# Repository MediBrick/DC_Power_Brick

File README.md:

# Power Brick

The Power Brick can control power to resistive heater, thermo electric cooler/heater or DC motor.
It requires 8V or larger input and might be able to handle 30A (4 oz copper).

## Two Channel DC Power Controller.
  - DRV8704 FET driver
  -  8..52V
  -  SPI interface for  monitoring
  -  PWM 500kHz
  -  CSD18540Q5B FET 30 / 400A (peak)

[Datasheet Driver](./datasheets/drv8704.pdf)
[Datasheet FET](./datasheets/csd18540q5b.pdf)

### Overview

### Control Logic

## 2x Two Channel Precision Thermistor ADC
  - ADS1220
  - Configured for two channel 10K NTC thermistor measurements using internal current source and external reference 22k resistor.

[Datasheet ADS1220](./datasheets/ads1220.pdf)

This design requires that both temperature sensors are attached. If one is not populated, the measurement circuit is interrupted and no temperature is reported.

## Power Brick PCB Design

The following files were created for this project using KiCad.

[Bill of Materials](./DC%20Power%20Brick%20BOM.xlsx)
[Gerber Files](./)

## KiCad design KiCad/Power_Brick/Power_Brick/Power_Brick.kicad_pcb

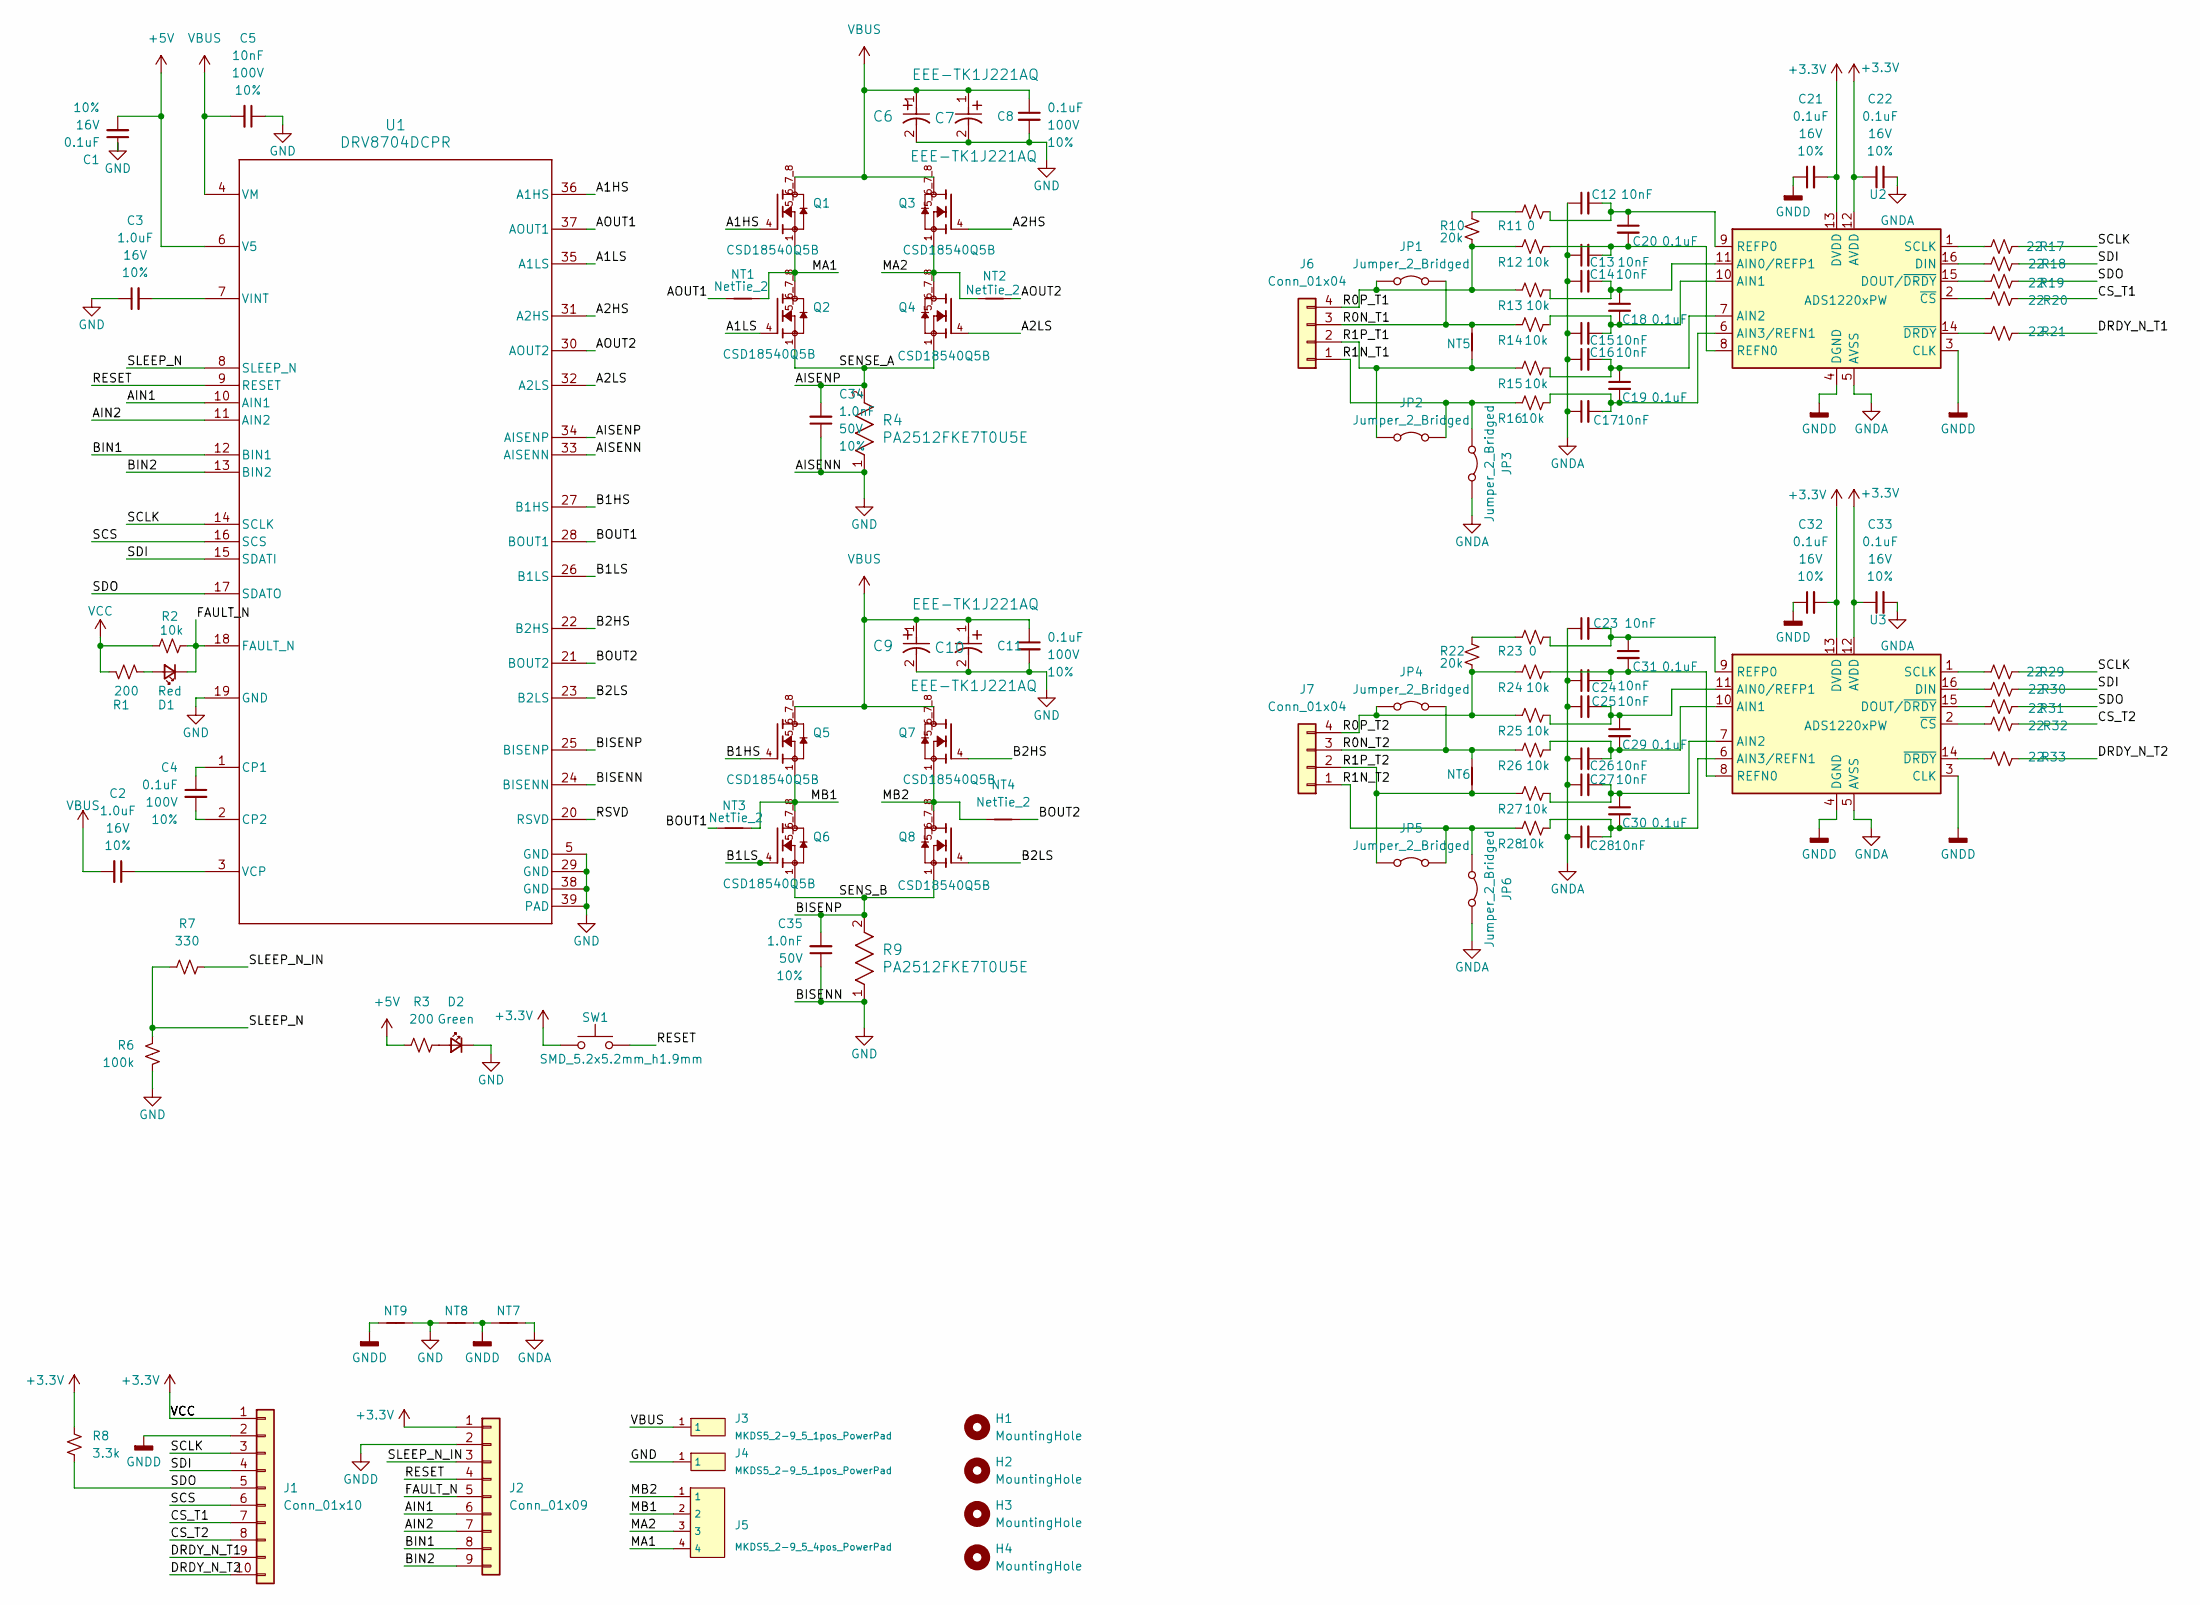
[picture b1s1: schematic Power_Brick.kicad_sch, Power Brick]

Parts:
C1, C18, C19, C20, C21, C22, C29, C30, C31, C32, C33: 0.1uF; C_0402_1005Metric; Voltage 16V; Tolerance 10%
C2, C3: 1.0uF; C_0402_1005Metric; Voltage 16V; Tolerance 10%
C4, C8, C11: 0.1uF; C_0603_1608Metric; Voltage 100V; Tolerance 10%
C5: 10nF; C_0402_1005Metric; Voltage 100V; Tolerance 10%
C6, C7, C9, C10: EEE-TK1J221AQ; CAP_PAN_EEE_H13_PAN
C12, C13, C14, C15, C16, C17, C23, C24, C25, C26, C27, C28: 10nF; C_0402_1005Metric; Voltage 50V; Tolerance 10%
C34, C35: 1.0nF; C_0402_1005Metric; Voltage 50V; Tolerance 10%
D1: Red; LED_0603_1608Metric_Red
D2: Green; LED_0603_1608Metric_Green
H1, H2, H3, H4: MountingHole; MountingHole_3.2mm_M3
J1: Conn_01x10; PinHeader_1x10_P2.54mm_Vertical
J2: Conn_01x09; PinHeader_1x09_P2.54mm_Vertical
J3, J4: MKDS5_2-9_5_1pos_PowerPad
J5: MKDS5_2-9_5_4pos_PowerPad
J6, J7: Conn_01x04; PinHeader_1x04_P2.54mm_Vertical
JP1, JP2, JP3, JP4, JP5, JP6: Jumper_2_Bridged; Jumper_2_NO
NT1, NT2, NT3, NT4, NT5, NT6: NetTie_2; NetTie-2_SMD_Pad0.25mm
NT7: NetTie_2; NetTie-2_SMD_Pad2.0mm
NT8, NT9: NetTie_2; NetTie-2_SMD_Pad0.5mm
Q1, Q2, Q3, Q4, Q5, Q6, Q7, Q8: CSD18540Q5B; TRANS_CSD18540Q5B; PARTREV B
R1, R3: 200; R_0402_1005Metric
R2, R12, R13, R14, R15, R16, R24, R25, R26, R27, R28: 10k; R_0402_1005Metric
R4, R9: PA2512FKE7T0U5E; RES_PA2512_YAG
R6: 100k; R_0402_1005Metric
R7: 330; R_0402_1005Metric
R8: 3.3k; R_0402_1005Metric
R10, R22: 20k; R_0402_1005Metric
R11, R23: 0; R_0402_1005Metric
R17, R18, R19, R20, R21, R29, R30, R31, R32, R33: 22; R_0402_1005Metric
SW1: SMD_5.2x5.2mm_h1.9mm; Push_SMD_4.6x2.8mm_h1.9mm
U1: DRV8704DCPR; DCP0038A_N
U2, U3: ADS1220xPW; TSSOP-16_4.4x5mm_P0.65mm

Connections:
+3.3V: C21.2, C22.1, C32.2, C33.1, J1.1, J2.1, R1.2, R2.1, R8.1, SW1.1, U2.12 (AVDD), U2.13 (DVDD), U3.12 (AVDD), U3.13 (DVDD)
+5V: C1.2, R3.1, U1.6 (V5)
/A1HS: Q1.4, U1.36 (A1HS)
/A1LS: Q2.4, U1.35 (A1LS)
/A2HS: Q3.4, U1.31 (A2HS)
/A2LS: Q4.4, U1.32 (A2LS)
/AIN1: J2.6, U1.10 (AIN1)
/AIN2: J2.7, U1.11 (AIN2)
/AISENP: C34.2, Q2.1, Q2.2, Q2.3, Q4.1, Q4.2, Q4.3, R4.2, U1.34 (AISENP)
/AOUT1: NT1.1, U1.37 (AOUT1)
/AOUT2: NT2.2, U1.30 (AOUT2)
/B1HS: Q5.4, U1.27 (B1HS)
/B1LS: Q6.4, U1.26 (B1LS)
/B2HS: Q7.4, U1.22 (B2HS)
/B2LS: Q8.4, U1.23 (B2LS)
/BIN1: J2.8, U1.12 (BIN1)
/BIN2: J2.9, U1.13 (BIN2)
/BISENP: C35.2, Q6.1, Q6.2, Q6.3, Q8.1, Q8.2, Q8.3, R9.2, U1.25 (BISENP)
/BOUT1: NT3.1, U1.28 (BOUT1)
/BOUT2: NT4.2, U1.21 (BOUT2)
/CS_T1: J1.7, R20.2
/CS_T2: J1.8, R32.2
/DRDY_N_T1: J1.9, R21.2
/DRDY_N_T2: J1.10, R33.2
/FAULT_N: D1.1 (K), J2.5, R2.2, U1.18 (FAULT_N)
/MA1: J5.4, NT1.2, Q1.1, Q1.2, Q1.3, Q2.5_6_7_8
/MA2: J5.3, NT2.1, Q3.1, Q3.2, Q3.3, Q4.5_6_7_8
/MB1: J5.2, NT3.2, Q5.1, Q5.2, Q5.3, Q6.5_6_7_8
/MB2: J5.1, NT4.1, Q7.1, Q7.2, Q7.3, Q8.5_6_7_8
/R0N_T1: J6.3, JP1.2 (B), NT5.2, R14.1
/R0N_T2: J7.3, JP4.2 (B), NT6.2, R26.1
/R0P_T1: J6.4, JP1.1 (A), R10.2, R12.1, R13.1
/R0P_T2: J7.4, JP4.1 (A), R22.2, R24.1, R25.1
/R1N_T1: J6.1, JP2.2 (B), JP3.1 (A), R16.1
/R1N_T2: J7.1, JP5.2 (B), JP6.1 (A), R28.1
/R1P_T1: J6.2, JP2.1 (A), NT5.1, R15.1
/R1P_T2: J7.2, JP5.1 (A), NT6.1, R27.1
/RESET: J2.4, SW1.2, U1.9 (RESET)
/RSVD: U1.20 (RSVD)
/SCLK: J1.3, R17.2, R29.2, U1.14 (SCLK)
/SCS: J1.6, U1.16 (SCS)
/SDI: J1.4, R18.2, R30.2, U1.15 (SDATI)
/SDO: J1.5, R8.2, R19.2, R31.2, U1.17 (SDATO)
/SLEEP_N: R6.2, R7.1, U1.8 (SLEEP_N)
/SLEEP_N_IN: J2.3, R7.2
GND: C1.1, C3.1, C5.1, C6.2, C7.2, C8.2, C9.2, C10.2, C11.2, C34.1, C35.1, D2.1 (K), J4.1, NT8.1, NT9.2, R4.1, R6.1, R9.1, U1.5 (GND), U1.19 (GND), U1.24 (BISENN), U1.29 (GND), U1.33 (AISENN), U1.38 (GND), U1.39 (PAD)
GNDA: C12.1, C13.1, C14.1, C15.1, C16.1, C17.1, C22.2, C23.1, C24.1, C25.1, C26.1, C27.1, C28.1, C33.2, JP3.2 (B), JP6.2 (B), NT7.2, U2.5 (AVSS), U3.5 (AVSS)
GNDD: C21.1, C32.1, J1.2, J2.2, NT7.1, NT8.2, NT9.1, U2.3 (CLK), U2.4 (DGND), U3.3 (CLK), U3.4 (DGND)
unnamed: D1.2 (A), R1.1
unnamed: D2.2 (A), R3.2
unnamed: R10.1, R11.1
unnamed: R22.1, R23.1
unnamed: C4.1, U1.1 (CP1)
unnamed: C4.2, U1.2 (CP2)
unnamed: C2.1, U1.3 (VCP)
unnamed: C3.2, U1.7 (VINT)
unnamed: C14.2, C18.1, R13.2, U2.11 (AIN0/REFP1)
unnamed: C15.2, C18.2, R14.2, U2.10 (AIN1)
unnamed: C16.2, C19.1, R15.2, U2.7 (AIN2)
unnamed: C17.2, C19.2, R16.2, U2.6 (AIN3/REFN1)
unnamed: R18.1, U2.16 (DIN)
unnamed: R19.1, U2.15 (DOUT/~DRDY)
unnamed: C13.2, C20.2, R12.2, U2.8 (REFN0)
unnamed: C12.2, C20.1, R11.2, U2.9 (REFP0)
unnamed: R17.1, U2.1 (SCLK)
unnamed: R20.1, U2.2 (~CS)
unnamed: R21.1, U2.14 (~DRDY)
unnamed: C25.2, C29.1, R25.2, U3.11 (AIN0/REFP1)
unnamed: C26.2, C29.2, R26.2, U3.10 (AIN1)
unnamed: C27.2, C30.1, R27.2, U3.7 (AIN2)
unnamed: C28.2, C30.2, R28.2, U3.6 (AIN3/REFN1)
unnamed: R30.1, U3.16 (DIN)
unnamed: R31.1, U3.15 (DOUT/~DRDY)
unnamed: C24.2, C31.2, R24.2, U3.8 (REFN0)
unnamed: C23.2, C31.1, R23.2, U3.9 (REFP0)
unnamed: R29.1, U3.1 (SCLK)
unnamed: R32.1, U3.2 (~CS)
unnamed: R33.1, U3.14 (~DRDY)
VBUS: C2.2, C5.2, C6.1, C7.1, C8.1, C9.1, C10.1, C11.1, J3.1, Q1.5_6_7_8, Q3.5_6_7_8, Q5.5_6_7_8, Q7.5_6_7_8, U1.4 (VM)

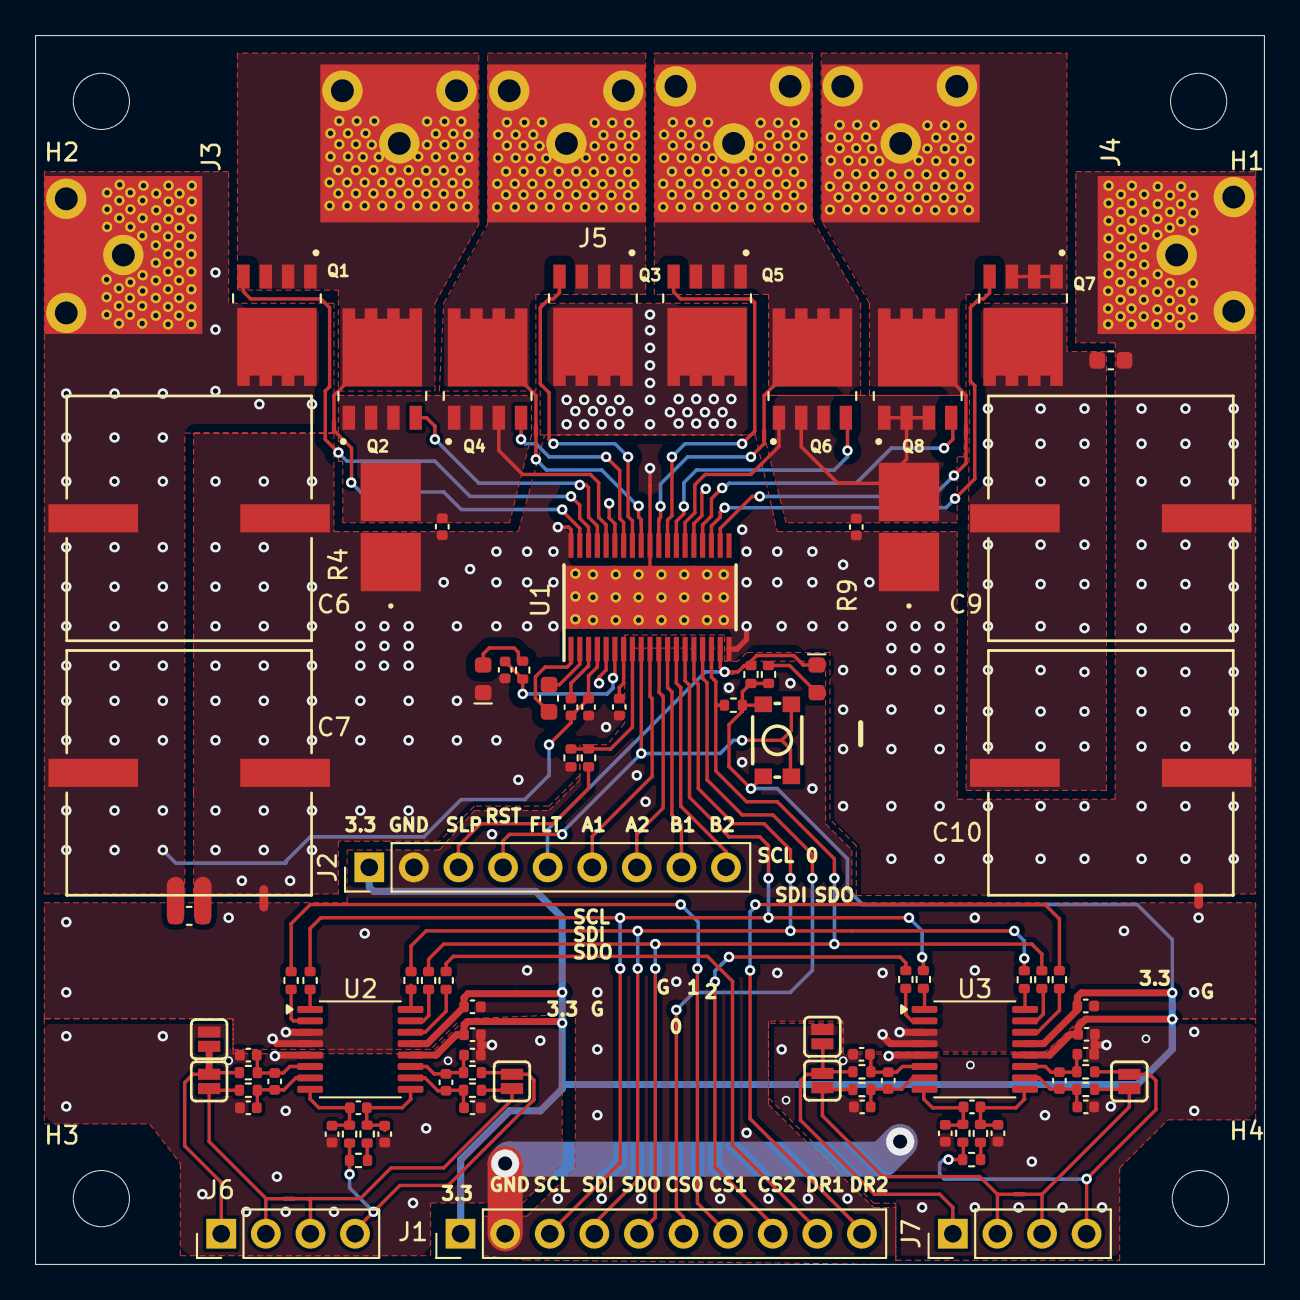
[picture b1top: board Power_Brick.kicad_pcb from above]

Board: 2 copper layers, 70.0 x 70.0 mm, 107 parts (0 on the bottom side), 78 nets.

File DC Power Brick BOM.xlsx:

Item # | Designator | Qty | Manufacturer | Mfg Part # | LCSC Part# | U.S. Distributor | Description / Value | Packaging | Type | Cost | Footprint | Remark
1 | C17,C26,C15,C5,C13,C24,C16,C12,C14,C28,C27,C23,C25 | 13 | Samsung Electro-Mechanics | CL05B103KC5VPNC | C16193410 |  | 10nF X7R ±10% 100V 0402 Ceramic Capacitors RoHS | 402 | SMD |  | C_0402_1005Metric
2 | Q2,Q8,Q6,Q5,Q4,Q3,Q7,Q1 | 8 | TI | CSD18540Q5B | C86513 |  | CSD18540Q5B MOSFET N CH 60V |  | SMD | 1.5 | TRANS_CSD18540Q5B
3 | R25,R14,R28,R13,R2,R16,R26,R12,R24,R15,R27 | 11 | YAGEO | RC0402FR-0710KL | C60490 |  | RES 10kΩ ±1% 62.5mW 0402 | 402 | SMD |  | R_0402_1005Metric
4 | C10,C7,C6,C9 | 4 | PANASONIC | EEETK1J221AQ | C401915 | Digikey Link incase LCSC is outofstock | CAP ALUM 220uF ±20% 63V SMD |  | SMD | 3 | CAP_PAN_EEE_H13_PAN
5 | R32,R19,R29,R21,R31,R33,R30,R20,R18,R17 | 10 | YAGEO | RC0402FR-0722RL | C114765 |  | RES 22Ω ±1% 62.5mW 0402 | 402 | SMD |  | R_0402_1005Metric
6 | R10,R22 | 2 | YAGEO | RC0402FR-0720KL | C93942 |  | RES 20kΩ ±1% 62.5mW 0402 | 402 | SMD |  | R_0402_1005Metric
7 | C4,C8,C11 | 3 | Samsung Electro-Mechanics | CL10B104KC8NNNC | C15725 |  | CAP CER 100nF 100V X7R 0603 | 603 | SMD |  | C_0603_1608Metric
8 | C34,C35 | 2 | Samsung Electro-Mechanics | CL05B102KC5VPNC | C2976448 |  | CAP CER 1nF 100V X7R 0402 | 402 | SMD |  | C_0402_1005Metric
9 | R3,R1 | 2 | YAGEO | RC0402FR-07200RL | C114764 |  | RES 200Ω ±1% 62.5mW 0402 | 402 | SMD |  | R_0402_1005Metric
10 | C3,C2 | 2 | Samsung Electro-Mechanics | CL05A105KO5NNNC | C29266 |  | CAP CER 1uF 16V X5R 0402 | 402 | SMD |  | C_0402_1005Metric
11 | C30,C31,C20,C33,C22,C32,C21,C29,C19,C18,C1 | 11 | Samsung Electro-Mechanics | CL05B104KO5NNNC | C1525 |  | CAP CER 100nF 16V X7R 0402 | 402 | SMD |  | C_0402_1005Metric
12 | R23,R11 | 2 | YAGEO | RC0402FR-070RL | C106231 |  | RES 0Ω ±1% 62.5mW 0402 | 402 | SMD |  | R_0402_1005Metric
13 | R4,R9 | 2 | YAGEO | PA2512FKE7T0U5E | C6730280 |  | RES 0.5mΩ ±1% 3W 2512, Current Sense | 2512 | SMD |  | RES_PA2512_YAG
14 | R7 | 1 | YAGEO | RC0402FR-07330RL | C105875 |  | RES 330Ω ±1% 62.5mW 0402 | 402 | SMD |  | R_0402_1005Metric
15 | R6 | 1 | YAGEO | RC0402FR-07100KL | C60491 |  | RES 100kΩ ±1% 62.5mW 0402 | 402 | SMD |  | R_0402_1005Metric
16 | R8 | 1 | YAGEO | RC0402FR-073K3L | C137992 |  | RES 3.3kΩ ±1% 62.5mW 0402 | 402 | SMD |  | R_0402_1005Metric
17 | U1 | 1 | TI | DRV8704DCPR | C701787 |  | HTSSOP-38-EP-4.4mm Motor Drivers, Controllers RoHS | HTSSOP-38-EP-4.4mm | SMD | 6 | DCP0038A_N
18 | U2,U3 | 2 | TI | ADS1220IPW | C1542855 | Digikey Link incase LCSC is outofstock | -40℃~+125℃ SPI 2.3V~5.5V 2kHz TSSOP-16 Analog to Digital Converters (ADC) RoHS | TSSOP-16 | SMD | 11 | TSSOP-16_4.4x5mm_P0.65mm
19 | D1 | 1 | XINGLIGHT | XL-1608SURC-06 | C965799 |  | Red LED | 603 | SMD |  | LED_0603_1608Metric_Red
20 | D2 | 1 | XINGLIGHT | XL-1608UGC-06A | C7371903 |  | Green LED | 603 | SMD |  | LED_0603_1608Metric_Green
21 | SW1 | 1 | C&K | KMR211NGLFS | C221676 |  | SWITCH TACTILE SPST-NO 120gf SMD |  | SMD |  | Push_SMD_4.6x2.8mm_h1.9mm
22 | JP1,JP2,JP4,JP5,JP3,JP6 | 6 |  |  |  |  | Jumper_2_Bridged |  |  |  | Jumper_2_NO | DO NOT POPULATE
23 | J1 | 1 |  |  |  |  | Conn_01x10 |  | SMD |  | PinHeader_1x10_P2.54mm_Vertical | DO NOT POPULATE
24 | J6,J7 | 2 |  |  |  |  | Conn_01x04 |  | SMD |  | PinHeader_1x04_P2.54mm_Vertical | DO NOT POPULATE
25 | J4,J3 | 2 |  |  |  |  | MKDS5_2-9_5_1pos_PowerPad |  | SMD |  | MKDS5_2-9_5_1pos_PowerPad | DO NOT POPULATE
26 | J2 | 1 |  |  |  |  | Conn_01x09 |  | SMD |  | PinHeader_1x09_P2.54mm_Vertical | DO NOT POPULATE
27 | J5 | 1 |  |  |  |  | MKDS5_2-9_5_4pos_PowerPad |  | SMD |  | MKDS5_2-9_5_4pos_PowerPad | DO NOT POPULATE

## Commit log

2025-12-08 Add project title to README
2025-12-11 TI options
2025-12-12 KiCad beta
2025-12-16 Beta Design
2026-01-28 Revised fault and capacitor ratings
2026-01-28 Revised fault and capacior ratings
2026-01-28 DRC, Silkscreen Updates
2026-02-03 Digital Grount Updates
2026-02-03 Cleanup
2026-02-08 4 oz copper 0.3mm clearance
